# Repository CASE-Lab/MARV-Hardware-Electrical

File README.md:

# MARV-Hardware-Electrical
Contains the electrical design files fo the MARV system. These includes the PCBs and system wiring diagram and specific wire function diagram. Some of the PCB projects includes a component library, otherwise the CASE-Association case-eagle-libraries have been used, found here: https://github.com/CASE-Association/case-eagle-libraries.git

This project uses both Eagle and KiCad ECAD programs. This is shown by folder names.

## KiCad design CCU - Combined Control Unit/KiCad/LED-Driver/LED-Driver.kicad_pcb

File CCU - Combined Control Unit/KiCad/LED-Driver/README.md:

# MIDI Fuse LED Driver

Led driver with integrated eFuse and PWM dimming in a MIDI fuse format. Provides undervoltage cutoff for battery protection and a low standby current of 30 uA.

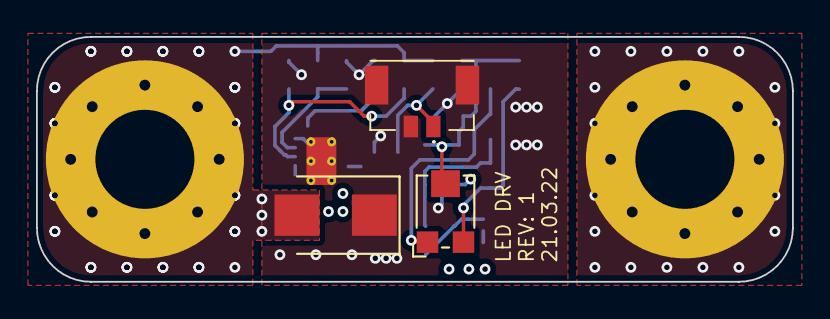
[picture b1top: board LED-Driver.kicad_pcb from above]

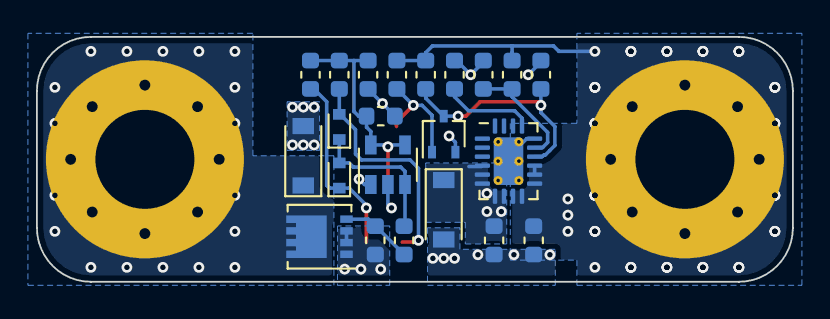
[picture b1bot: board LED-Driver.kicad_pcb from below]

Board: 4 copper layers, 42.0 x 13.6 mm, 27 parts (22 on the bottom side), 13 nets.

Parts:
C1, C2: 0.1 uF; C_0603_1608Metric
C3: 2.2uF 16V; C_0603_1608Metric
C4: ?; C_0603_1608Metric
D1, D5: D_Schottky; D_SOD-123
D2, D3: RB751S40T5G; D_SOD-523
D4: D_TVS; D_SMB
J1, J2: Conn_01x01; MountingHole_5.5mm_Pad_Via
J3: Conn_01x02; Molex_Micro-Lock_5055680271_1x02_P1.25_Vertical
Q1: 2N7002PW; SOT-323_SC-70
Q2: DMP3013SFV; Diodes_PowerDI3333-8
R1: 130k; R_0603_1608Metric
R2, R5: 1.5M; R_0603_1608Metric
R3, R6, R9: 100k; R_0603_1608Metric
R4: 18k; R_0603_1608Metric
R7, R8: R; R_0603_1608Metric
R10: 1k; R_0603_1608Metric
RV1: 100k; Potentiometer_Bourns_TC33X_Vertical
U1: MIC1555YM5-TR; SOT-23-5
U2: TPS25940x-Q1; QFN-20-1EP_3x4mm_P0.5mm_EP1.65x2.65mm_ThermalVias

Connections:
+12V: C1.1, D1.1, Q2.1, Q2.2, Q2.3, R9.2, U1.1, U2.4, U2.5, U2.6, U2.7, U2.8
+BATT: C2.1, D4.2, J1.1, R2.1, R5.1, R6.1, U2.9, U2.10, U2.11, U2.12, U2.13
/GATE: Q2.4, R9.1, R10.1
/LED_OUT: D5.1, J2.1, Q2.5
/PWM: D2.2, D3.1, R10.2, U1.3
/TRG_THR: C3.1, C4.1, R7.2, R8.2, RV1.2, U1.4, U1.5
/eFuse/~EN: J3.1, Q1.1, R6.2
GND: C1.2, C2.2, C3.2, C4.2, D1.2, D4.1, D5.2, J3.2, J3.MP, Q1.2, R1.2, R3.2, R4.2, U1.2, U2.16, U2.21
unnamed: D2.1, R7.1, RV1.3
unnamed: D3.2, R8.1, RV1.1
unnamed: Q1.3, R1.1, R5.2, U2.14
unnamed: R2.2, R3.1, U2.15
unnamed: R4.1, U2.17

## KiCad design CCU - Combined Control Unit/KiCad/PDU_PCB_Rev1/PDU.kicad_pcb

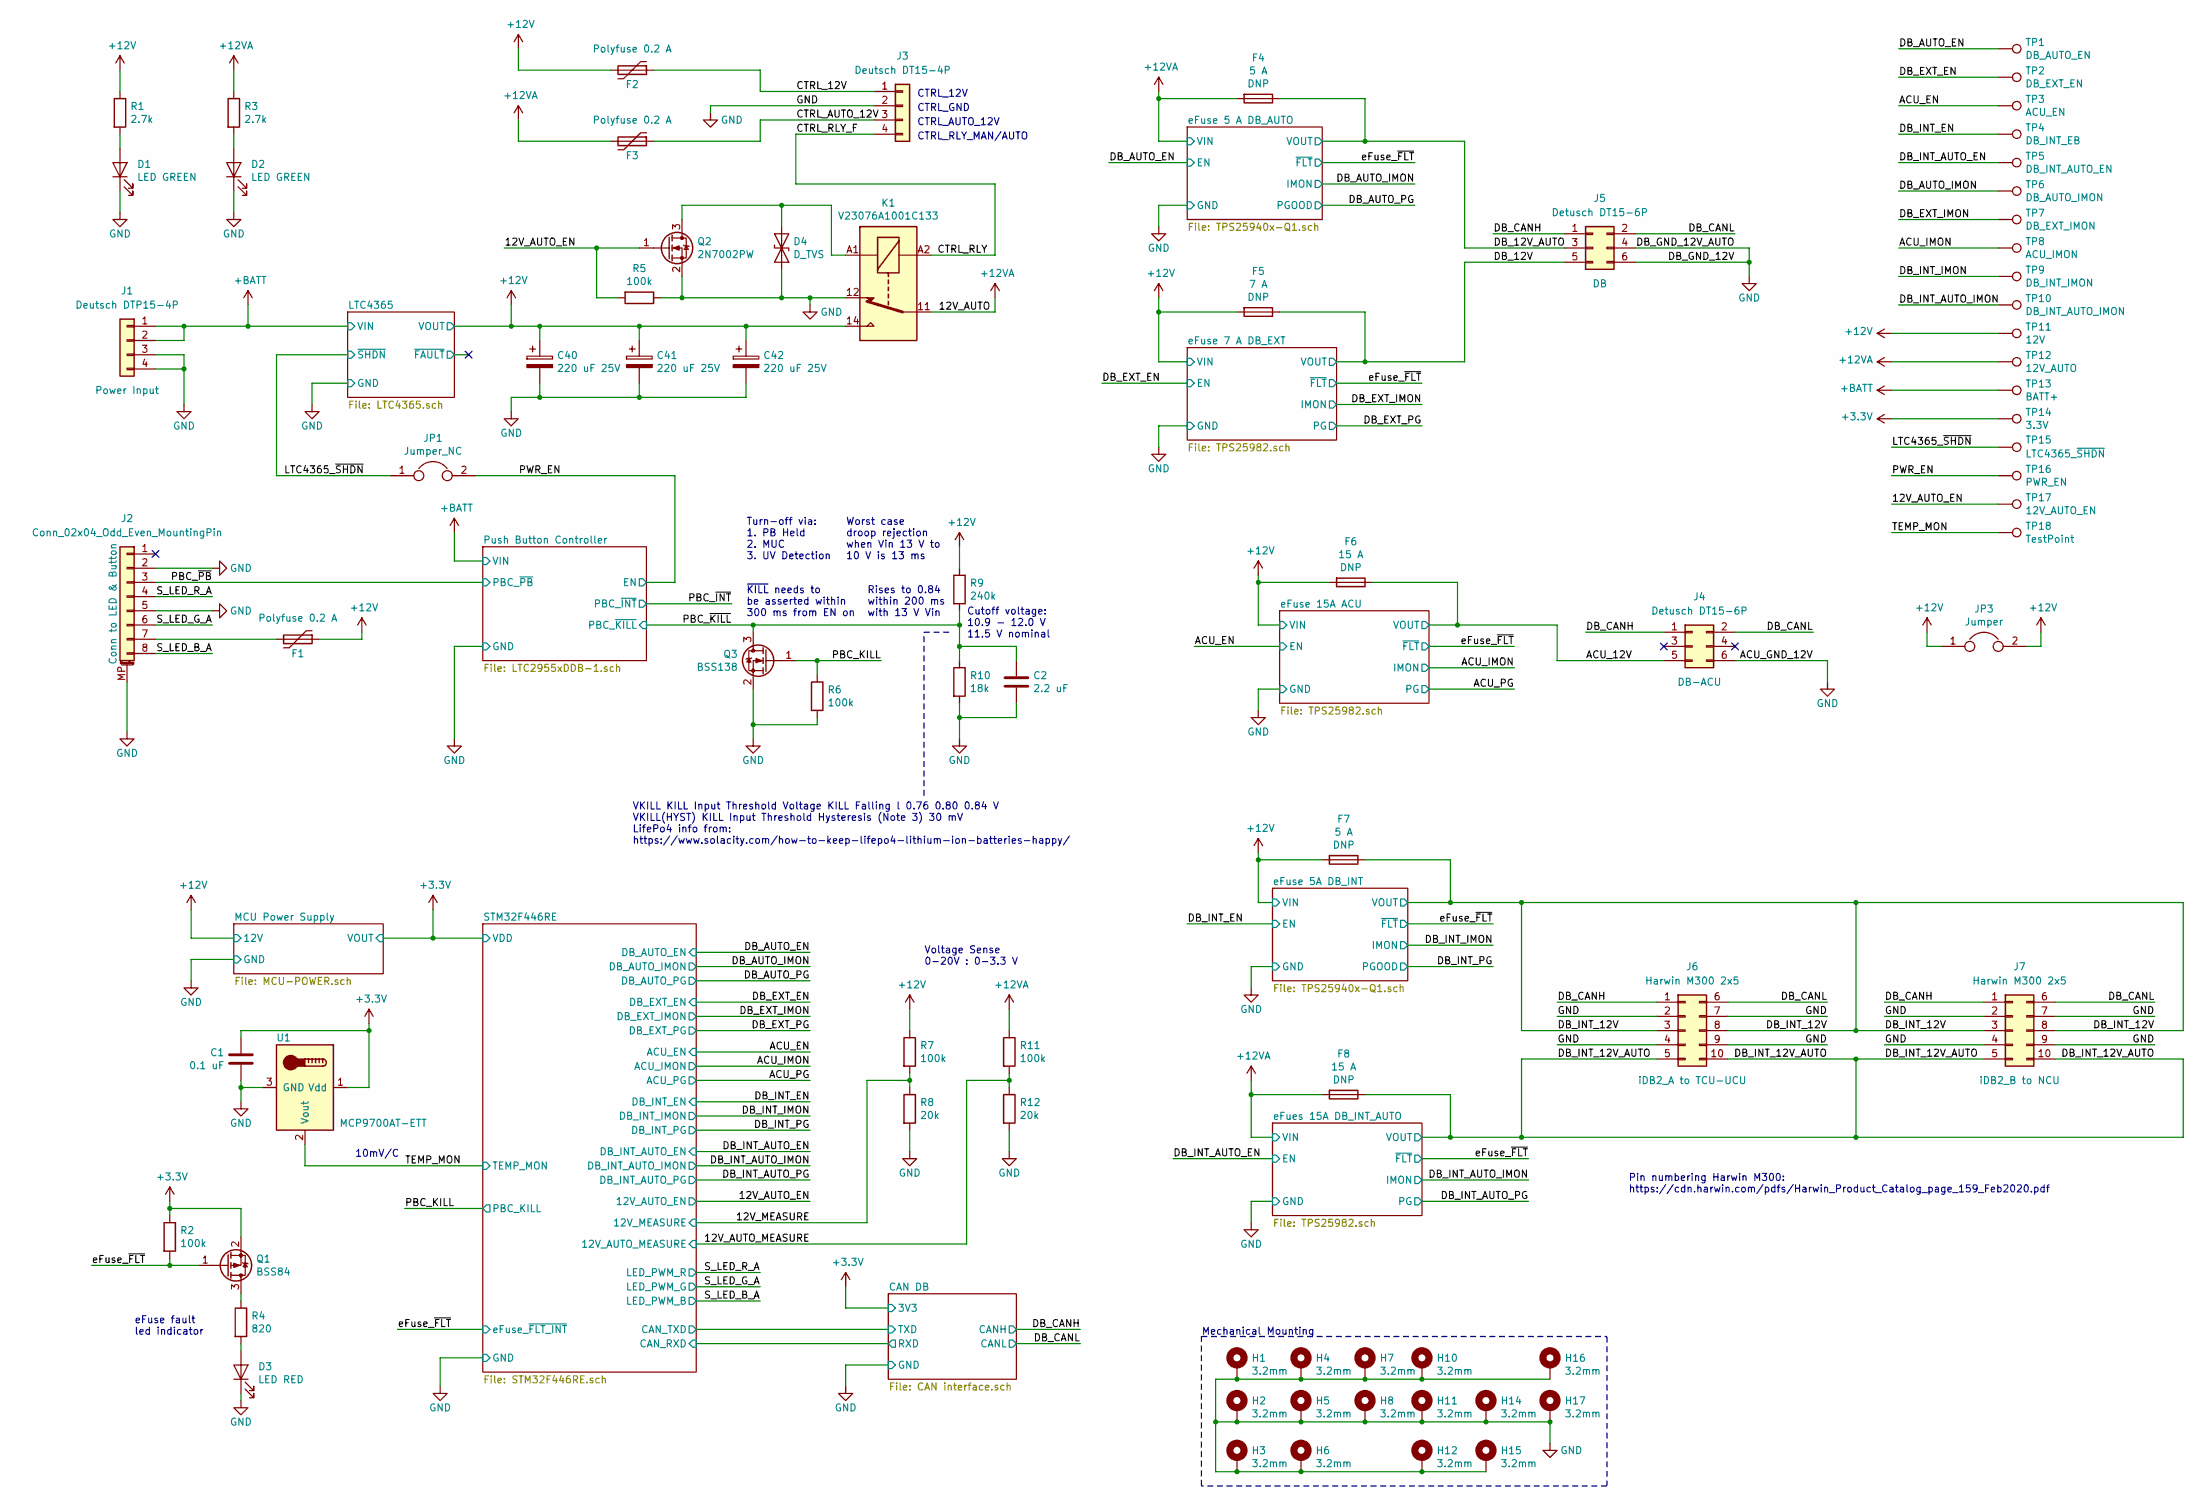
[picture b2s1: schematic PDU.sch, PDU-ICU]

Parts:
C1: 0.1 uF; C_0603_1608Metric
C2: 2.2 uF; C_0603_1608Metric
C40, C41, C42: 220 uF 25V; CP_Radial_D8.0mm_P3.50mm; MPN ESE227M025AG3AA
D1, D2: LED GREEN; LED_0603_1608Metric
D3: LED RED; LED_0603_1608Metric
D4: D_TVS; D_SMB; MPN TPSMB20CA
F1, F2, F3: Polyfuse 0.2 A; R_1206_3216Metric; MPN NANOSMDC020F-2
F4, F7: 5 A; Fuse_2010_5025Metric_Pad1.52x2.65mm_HandSolder; MPN 0453005
F5: 7 A; Fuse_2010_5025Metric_Pad1.52x2.65mm_HandSolder; MPN 0453007
F6, F8: 15 A; Fuse_2010_5025Metric_Pad1.52x2.65mm_HandSolder; MPN 0453012
H1, H2, H3, H4, H5, H6, H7, H8, H10, H11, H12, H14, H15, H16, H17: 3.2mm; MountingHole_3.2mm_M3_Pad_Via
J1: Deutsch DTP15-4P; Deutsch_DTP15-4P_2x2
J2: Conn_02x04_Odd_Even_MountingPin; Molex_Micro-Lock_5054330871_2x4_P1.25_Vertical; MPN 538-505433-0871
J3: Deutsch DT15-4P; Deutsch_DT15-4P_2x2
J4, J5: Detusch DT15-6P; Detusch_DT15-6P_2x3
J6, J7: Harwin M300 2x5; Harwin_M300_M300MV31045M1_2x5_P3.0_Vertical
JP1: Jumper_NC; R_0603_1608Metric
JP3: Jumper; Keystone_5104; MPN 5104
K1: V23076A1001C133; TE_Relay_V23076A1001C133
Q1: BSS84; SOT-23; MPN BSS84
Q2: 2N7002PW; SOT-323_SC-70
Q3: BSS138; SOT-23
R1, R3: 2.7k; R_0603_1608Metric
R2, R5, R6, R7, R11: 100k; R_0603_1608Metric
R4: 820; R_0603_1608Metric
R8, R12: 20k; R_0603_1608Metric
R9: 240k; R_0603_1608Metric
R10: 18k; R_0603_1608Metric
TP1: DB_AUTO_EN; TestPoint_THTPad_D1.0mm_Drill0.5mm
TP2: DB_EXT_EN; TestPoint_THTPad_D1.0mm_Drill0.5mm
TP3: ACU_EN; TestPoint_THTPad_D1.0mm_Drill0.5mm
TP4: DB_INT_EB; TestPoint_THTPad_D1.0mm_Drill0.5mm
TP5: DB_INT_AUTO_EN; TestPoint_THTPad_D1.0mm_Drill0.5mm
TP6: DB_AUTO_IMON; TestPoint_THTPad_D1.0mm_Drill0.5mm
TP7: DB_EXT_IMON; TestPoint_THTPad_D1.0mm_Drill0.5mm
TP8: ACU_IMON; TestPoint_THTPad_D1.0mm_Drill0.5mm
TP9: DB_INT_IMON; TestPoint_THTPad_D1.0mm_Drill0.5mm
TP10: DB_INT_AUTO_IMON; TestPoint_THTPad_D1.0mm_Drill0.5mm
TP11: 12V; TestPoint_THTPad_D1.0mm_Drill0.5mm
TP12: 12V_AUTO; TestPoint_THTPad_D1.0mm_Drill0.5mm
TP13: BATT+; TestPoint_THTPad_D1.0mm_Drill0.5mm
TP14: 3.3V; TestPoint_THTPad_D1.0mm_Drill0.5mm
TP15: LTC4365_~SHDN; TestPoint_THTPad_D1.0mm_Drill0.5mm
TP16: PWR_EN; TestPoint_THTPad_D1.0mm_Drill0.5mm
TP17: 12V_AUTO_EN; TestPoint_THTPad_D1.0mm_Drill0.5mm
TP18: TestPoint; TestPoint_THTPad_D1.0mm_Drill0.5mm
U1: MCP9700AT-ETT; SOT-23; MPN MCP9700AT-E/TT

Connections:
+3V3: C1.1, Q1.2 (S), R2.1, TP14.1, U1.1 (Vdd); also elsewhere on the board
+12V: C40.1, C41.1, C42.1, F1.1, F2.2, F5.2, F6.2, F7.2, JP3.1, JP3.2, K1.14, R1.1, R7.1, R9.1, TP11.1; also elsewhere on the board
+12VA: F3.2, F4.2, F8.2, K1.11, R3.1, R11.1, TP12.1; also elsewhere on the board
+BATT: J1.1, J1.2, TP13.1; also elsewhere on the board
/12V_AUTO_EN: Q2.1 (G), R5.2, TP17.1; also elsewhere on the board
/12V_AUTO_MEASURE: R11.2, R12.1; also elsewhere on the board
/12V_MEASURE: R7.2, R8.1; also elsewhere on the board
/ACU_12V: F6.1, J4.5; also elsewhere on the board
/ACU_EN: TP3.1; also elsewhere on the board
/ACU_IMON: TP8.1; also elsewhere on the board
/CTRL_12V: F2.1, J3.1
/CTRL_AUTO_12V: F3.1, J3.3
/CTRL_RLY: J3.4, K1.A2
/DB_AUTO_EN: TP1.1; also elsewhere on the board
/DB_AUTO_IMON: TP6.1; also elsewhere on the board
/DB_CANH: J4.1, J5.1, J6.1, J7.1; also elsewhere on the board
/DB_CANL: J4.2, J5.2, J6.6, J7.6; also elsewhere on the board
/DB_EXT_EN: TP2.1; also elsewhere on the board
/DB_EXT_IMON: TP7.1; also elsewhere on the board
/DB_INT_AUTO_EN: TP5.1; also elsewhere on the board
/DB_INT_AUTO_IMON: TP10.1; also elsewhere on the board
/DB_INT_EN: TP4.1; also elsewhere on the board
/DB_INT_IMON: TP9.1; also elsewhere on the board
/LTC4365_~SHDN: JP1.1, TP15.1; also elsewhere on the board
/PBC_KILL: Q3.1 (G), R6.1; also elsewhere on the board
/PBC_~KILL: C2.1, Q3.3 (D), R9.2, R10.1; also elsewhere on the board
/PBC_~PB: J2.3; also elsewhere on the board
/PWR_EN: JP1.2, TP16.1; also elsewhere on the board
/S_LED_B_A: J2.8; also elsewhere on the board
/S_LED_G_A: J2.6; also elsewhere on the board
/S_LED_R_A: J2.4; also elsewhere on the board
/TEMP_MON: TP18.1, U1.2 (Vout); also elsewhere on the board
/eFuse_~FLT: Q1.1 (G), R2.2; also elsewhere on the board
GND: C1.2, C2.2, C40.2, C41.2, C42.2, D1.1 (K), D2.1 (K), D3.1 (K), D4.2 (A2), H1.1, H2.1, H3.1, H4.1, H5.1, H6.1, H7.1, H8.1, H10.1, H11.1, H12.1, H14.1, H15.1, H16.1, H17.1, J1.3, J1.4, J2.2, J2.5, J2.MP (MountPin), J3.2, J4.6, J5.4, J5.6, J6.2, J6.4, J6.7, J6.9, J7.2, J7.4, J7.7, J7.9, K1.12, Q2.2 (S), Q3.2 (S), R5.1, R6.2, R8.2, R10.2, R12.2, U1.3 (GND); also elsewhere on the board
unnamed: D1.2 (A), R1.2
unnamed: D2.2 (A), R3.2
unnamed: D3.2 (A), R4.2
unnamed: D4.1 (A1), K1.A1, Q2.3 (D)
unnamed: F1.2, J2.7
unnamed: Q1.3 (D), R4.1

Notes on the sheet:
Mechanical Mounting
CTRL_12V
CTRL_GND
CTRL_AUTO_12V
CTRL_RLY_MAN/AUTO
Turn-off via: 1. PB Held 2. MUC 3. UV Detection
Pin numbering Harwin M300: https://cdn.harwin.com/pdfs/Harwin_Product_Catalog_page_159_Feb2020.pdf
eFuse fault led indicator
Voltage Sense 0-20V : 0-3.3 V
10mV/C
VKILL KILL Input Threshold Voltage KILL Falling l 0.76 0.80 0.84 V VKILL(HYST) KILL Input Threshold Hysteresis (Note 3) 30 mV LifePo4 info from: https://www.solacity.com/how-to-keep-lifepo4-lithium-ion-batteries-happy/
Cutoff voltage: 10.9 - 12.0 V 11.5 V nominal
~KILL~ needs to be asserted within 300 ms from EN on
Rises to 0.84 within 200 ms with 13 V Vin
Worst case droop rejection when Vin 13 V to 10 V is 13 ms

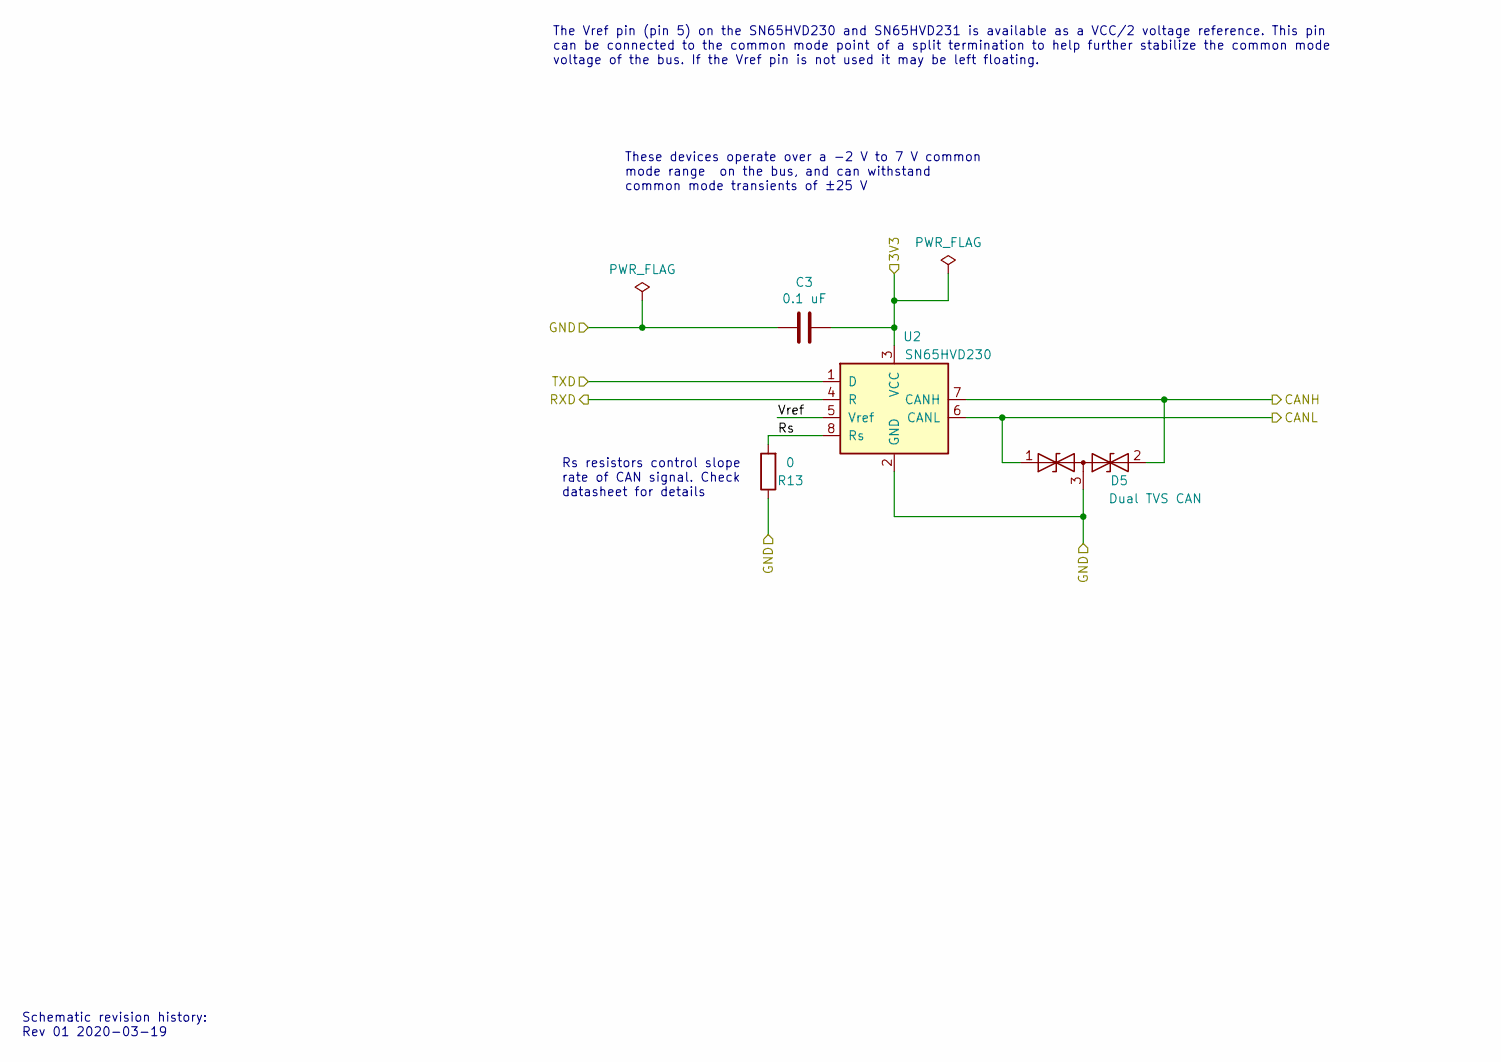
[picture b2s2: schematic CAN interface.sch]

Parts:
C3: 0.1 uF; C_0603_1608Metric
D5: Dual TVS CAN; SOT-23; MPN NUP2105L
R13: 0; R_0603_1608Metric
U2: SN65HVD230; SOIC-8_3.9x4.9mm_P1.27mm

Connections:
+3V3: C3.1, U2.3 (VCC); also elsewhere on the board
/CAN DB/Rs: R13.2, U2.8 (Rs)
/CAN DB/Vref: U2.5 (Vref)
/DB_CANH: D5.2 (A2), U2.7 (CANH); also elsewhere on the board
/DB_CANL: D5.1 (A1), U2.6 (CANL); also elsewhere on the board
/STM32F446RE/CAN_RXD: U2.4 (R); also elsewhere on the board
/STM32F446RE/CAN_TXD: U2.1 (D); also elsewhere on the board
GND: C3.2, D5.3 (common), R13.1, U2.2 (GND); also elsewhere on the board

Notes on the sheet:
These devices operate over a -2 V to 7 V common mode range on the bus, and can withstand common mode transients of ±25 V
Rs resistors control slope rate of CAN signal. Check datasheet for details
Schematic revision history: Rev 01 2020-03-19
The Vref pin (pin 5) on the SN65HVD230 and SN65HVD231 is available as a VCC/2 voltage reference. This pin can be connected to the common mode point of a split termination to help further stabilize the common mode voltage of the bus. If the Vref pin is not used it may be left floating.

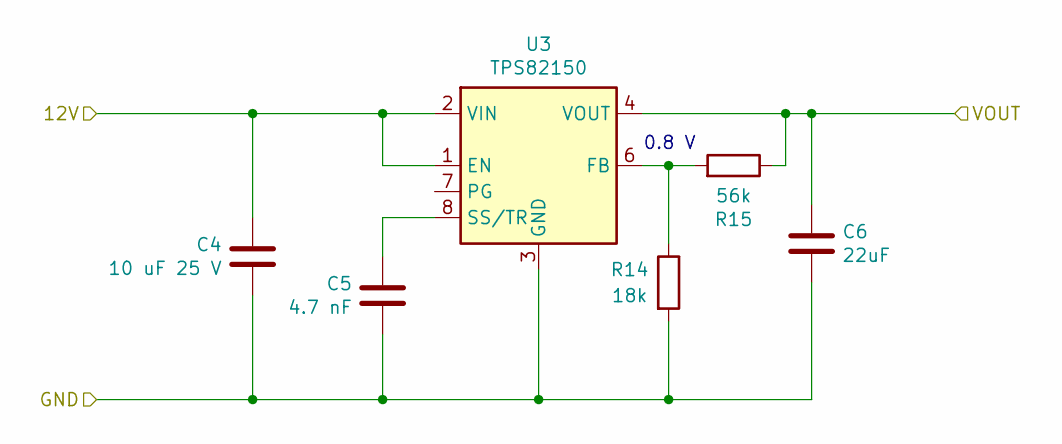
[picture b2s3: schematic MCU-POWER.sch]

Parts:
C4: 10 uF 25 V; C_1206_3216Metric
C5: 4.7 nF; C_0603_1608Metric
C6: 22uF; C_1206_3216Metric
R14: 18k; R_0603_1608Metric
R15: 56k; R_0603_1608Metric
U3: TPS82150; Texas_SIL0008D_MicroSiP-8-1EP_2.8x3mm_P0.65mm_EP1.1x1.9mm_T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; MPN TPS82150SILR

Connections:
+3V3: C6.1, R15.1, U3.4 (VOUT), U3.5 (VOUT); also elsewhere on the board
+12V: C4.1, U3.1 (EN), U3.2 (VIN); also elsewhere on the board
GND: C4.2, C5.2, C6.2, R14.2, U3.3 (GND), U3.9 (GND); also elsewhere on the board
unnamed: C5.1, U3.8 (SS/TR)
unnamed: R14.1, R15.2, U3.6 (FB)

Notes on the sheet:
0.8 V

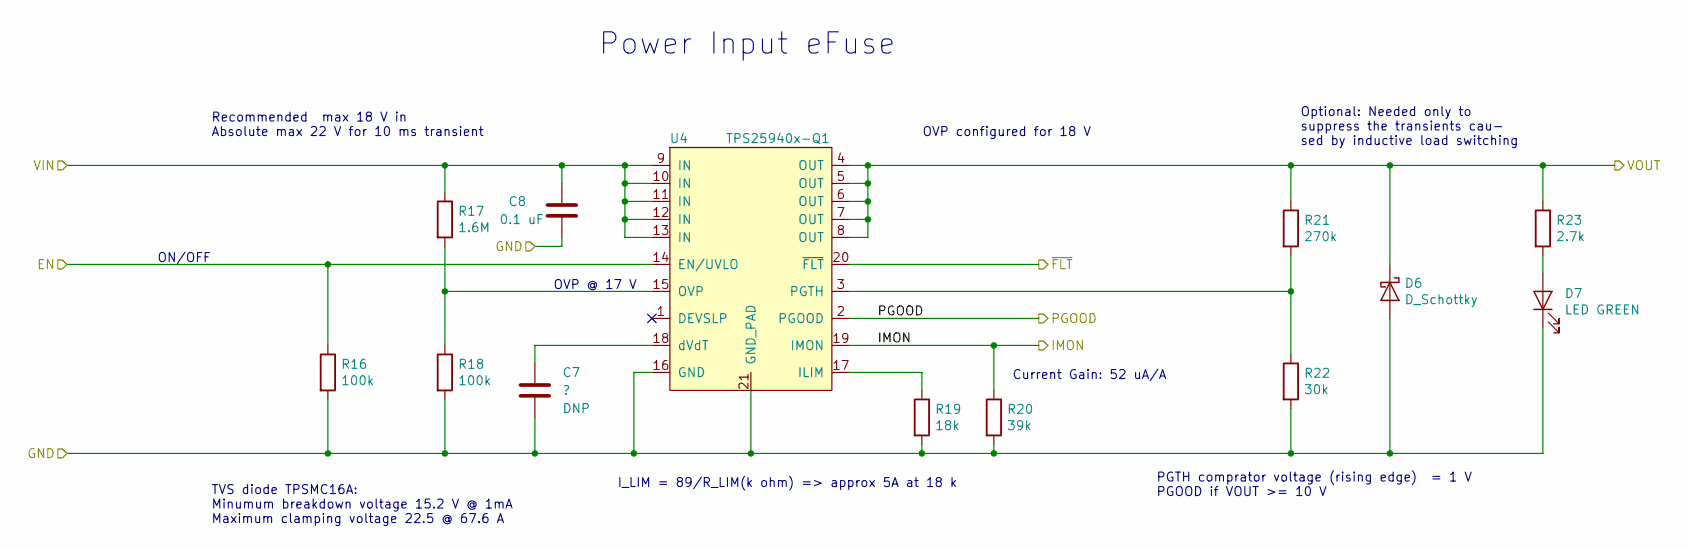
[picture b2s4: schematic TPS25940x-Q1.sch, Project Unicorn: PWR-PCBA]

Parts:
C7: ?; C_0603_1608Metric
C8: 0.1 uF; C_0603_1608Metric
D6: D_Schottky; D_SOD-123; MPN 1N5819HW
D17: LED GREEN; LED_0603_1608Metric
R16, R18: 100k; R_0603_1608Metric
R17: 1.6M; R_0603_1608Metric
R19: 18k; R_0603_1608Metric
R20: 39k; R_0603_1608Metric
R21: 270k; R_0603_1608Metric
R22: 30k; R_0603_1608Metric
R54: 2.7k; R_0603_1608Metric
U4: TPS25940x-Q1; QFN-20-1EP_3x4mm_P0.5mm_EP1.65x2.65mm_ThermalVias; MPN TPS25940LQRVCRQ1

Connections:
+12V: C8.1, R17.1, U4.9 (IN), U4.10 (IN), U4.11 (IN), U4.12 (IN), U4.13 (IN); also elsewhere on the board
/DB_INT_EN: R16.1, U4.14 (EN/UVLO); also elsewhere on the board
/DB_INT_IMON: R20.1, U4.19 (IMON); also elsewhere on the board
/DB_INT_PG: U4.2 (PGOOD); also elsewhere on the board
/eFuse_~FLT: U4.20 (~FLT); also elsewhere on the board
GND: C7.2, C8.2, D6.2 (A), D17.1 (K), R16.2, R18.2, R19.2, R20.2, R22.2, U4.16 (GND), U4.21 (GND_PAD); also elsewhere on the board
unnamed: C7.1, U4.18 (dVdT)
unnamed: D17.2 (A), R54.2
unnamed: R17.2, R18.1, U4.15 (OVP)
unnamed: R19.1, U4.17 (ILIM)
unnamed: R21.2, R22.1, U4.3 (PGTH)

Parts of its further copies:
C28: ?; C_0603_1608Metric
C29: 0.1 uF; C_0603_1608Metric
D7: LED GREEN; LED_0603_1608Metric
D16: D_Schottky; D_SOD-123; MPN 1N5819HW
R23: 2.7k; R_0603_1608Metric
R47, R49: 100k; R_0603_1608Metric
R48: 1.6M; R_0603_1608Metric
R50: 18k; R_0603_1608Metric
R51: 39k; R_0603_1608Metric
R52: 270k; R_0603_1608Metric
R53: 30k; R_0603_1608Metric
U10: TPS25940x-Q1; QFN-20-1EP_3x4mm_P0.5mm_EP1.65x2.65mm_ThermalVias; MPN TPS25940LQRVCRQ1

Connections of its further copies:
+12VA: C29.1, R48.1, U10.9 (IN), U10.10 (IN), U10.11 (IN), U10.12 (IN), U10.13 (IN); also elsewhere on the board
/DB_AUTO_EN: R47.1, U10.14 (EN/UVLO); also elsewhere on the board
/DB_AUTO_IMON: R51.1, U10.19 (IMON); also elsewhere on the board
/DB_AUTO_PG: U10.2 (PGOOD); also elsewhere on the board
/eFuse_~FLT: U10.20 (~FLT); also elsewhere on the board
GND: C28.2, C29.2, D7.1 (K), D16.2 (A), R47.2, R49.2, R50.2, R51.2, R53.2, U10.16 (GND), U10.21 (GND_PAD); also elsewhere on the board
unnamed: C28.1, U10.18 (dVdT)
unnamed: D7.2 (A), R23.2
unnamed: R48.2, R49.1, U10.15 (OVP)
unnamed: R50.1, U10.17 (ILIM)
unnamed: R52.2, R53.1, U10.3 (PGTH)

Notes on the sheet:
ON/OFF
Power Input eFuse
Recommended max 18 V in Absolute max 22 V for 10 ms transient
I_LIM = 89/R_LIM(k ohm) => approx 5A at 18 k
PGTH comprator voltage (rising edge) = 1 V PGOOD if VOUT >= 10 V
OVP configured for 18 V
Optional: Needed only to suppress the transients cau- sed by inductive load switching
TVS diode TPSMC16A: Minumum breakdown voltage 15.2 V @ 1mA Maximum clamping voltage 22.5 @ 67.6 A
OVP @ 17 V
Current Gain: 52 uA/A

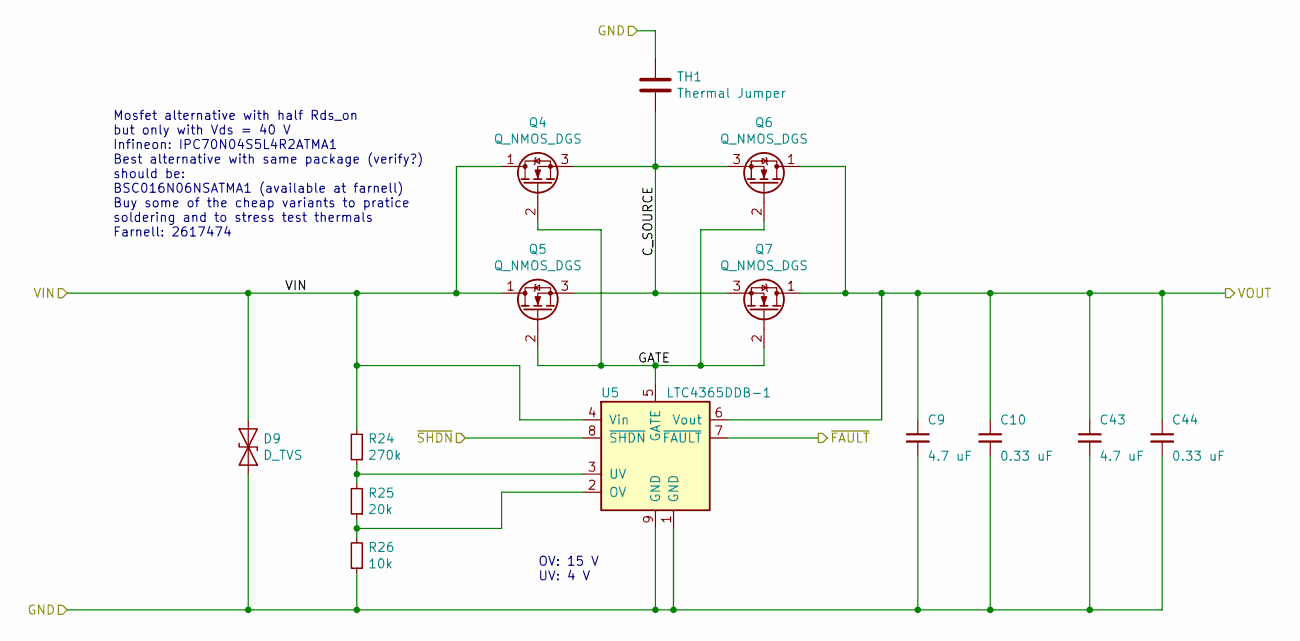
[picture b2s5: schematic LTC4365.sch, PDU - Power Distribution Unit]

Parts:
C9, C43: 4.7 uF; C_1206_3216Metric; MPN 12063C475K4T2A
C10, C44: 0.33 uF; C_0805_2012Metric
D9: D_TVS; D_SMC; MPN 5.0SMDJ24CA-Q
Q4, Q5, Q6, Q7: Q_NMOS_DGS; TDSON-8-1; MPN BSC016N06NSATMA1
R24: 270k; R_0603_1608Metric
R25: 20k; R_0603_1608Metric
R26: 10k; R_0603_1608Metric
TH1: Thermal Jumper; R_0612_1632Metric; MPN THJP0612AST1
U5: LTC4365DDB-1; DFN-8-1EP_2x3mm_P0.5mm_EP0.61x2.2mm; MPN LTC4365IDDB-1#TRMPBF

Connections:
+12V: C9.1, C10.1, C43.1, C44.1, Q6.1 (D), Q7.1 (D), U5.6 (Vout); also elsewhere on the board
+BATT: D9.1 (A1), Q4.1 (D), Q5.1 (D), R24.2, U5.4 (Vin); also elsewhere on the board
/LTC4365/C_SOURCE: Q4.3 (S), Q5.3 (S), Q6.3 (S), Q7.3 (S), TH1.2
/LTC4365/GATE: Q4.2 (G), Q5.2 (G), Q6.2 (G), Q7.2 (G), U5.5 (GATE)
/LTC4365/~FAULT: U5.7 (~FAULT)
/LTC4365_~SHDN: U5.8 (~SHDN); also elsewhere on the board
GND: C9.2, C10.2, C43.2, C44.2, D9.2 (A2), R26.1, TH1.1, U5.1 (GND), U5.9 (GND); also elsewhere on the board
unnamed: R24.1, R25.2, U5.3 (UV)
unnamed: R25.1, R26.2, U5.2 (OV)

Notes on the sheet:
OV: 15 V UV: 4 V
Mosfet alternative with half Rds_on but only with Vds = 40 V Infineon: IPC70N04S5L4R2ATMA1 Best alternative with same package (verify?) should be: BSC016N06NSATMA1 (available at farnell) Buy some of the cheap variants to pratice soldering and to stress test thermals Farnell: 2617474

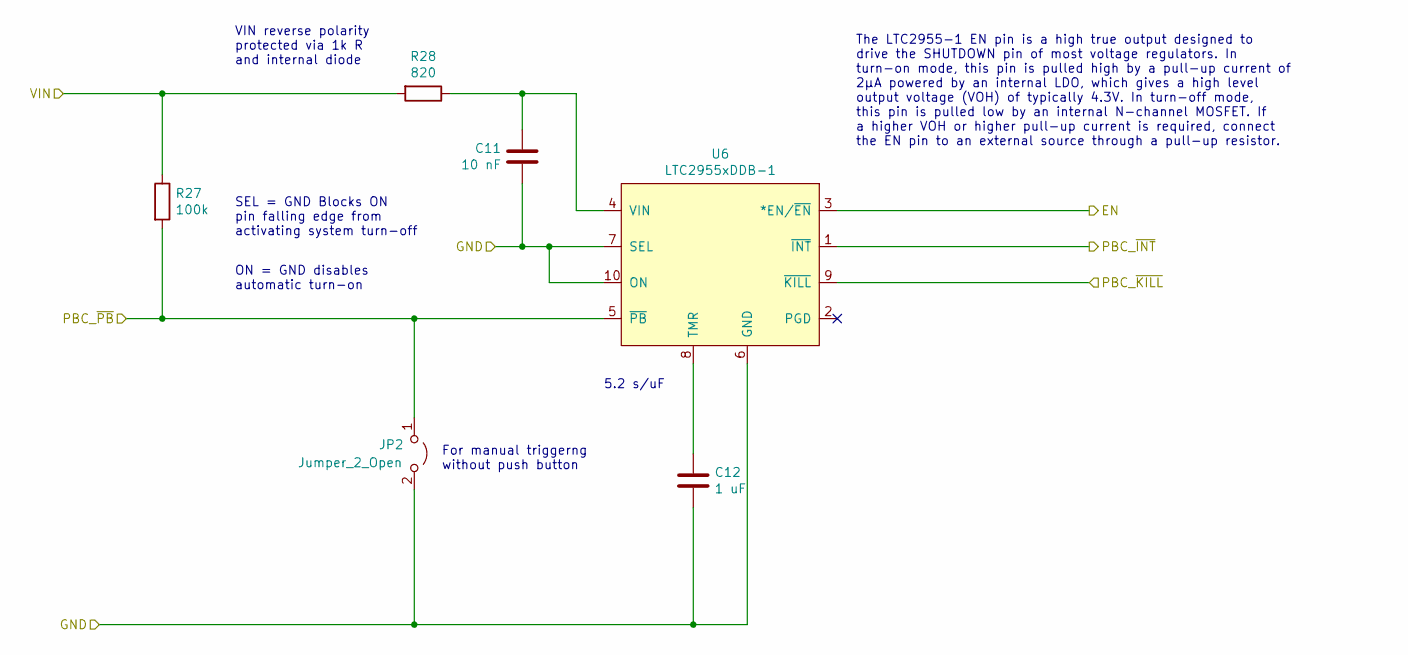
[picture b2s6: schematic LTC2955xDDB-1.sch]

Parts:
C11: 10 nF; C_0603_1608Metric
C12: 1 uF; C_0603_1608Metric
JP2: Jumper_2_Open; TestPoint_2Pads_Pitch2.54mm_Drill0.8mm
R27: 100k; R_0603_1608Metric
R28: 820; R_0603_1608Metric
U6: LTC2955xDDB-1; DFN-10-1EP_2x3mm_P0.5mm_EP0.64x2.4mm

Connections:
+BATT: R27.1, R28.2; also elsewhere on the board
/PBC_~INT: U6.1 (~INT)
/PBC_~KILL: U6.9 (~KILL); also elsewhere on the board
/PBC_~PB: JP2.1 (A), R27.2, U6.5 (~PB); also elsewhere on the board
/PWR_EN: U6.3 (*EN/~EN); also elsewhere on the board
GND: C11.2, C12.2, JP2.2 (B), U6.6 (GND), U6.7 (SEL), U6.10 (ON); also elsewhere on the board
unnamed: C11.1, R28.1, U6.4 (VIN)
unnamed: C12.1, U6.8 (TMR)

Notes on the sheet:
SEL = GND Blocks ON pin falling edge from activating system turn-off
5.2 s/uF
The LTC2955-1 EN pin is a high true output designed to drive the SHUTDOWN pin of most voltage regulators. In turn-on mode, this pin is pulled high by a pull-up current of 2µA powered by an internal LDO, which gives a high level output voltage (VOH) of typically 4.3V. In turn-off mode, this pin is p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
VIN reverse polarity protected via 1k R and internal diode
ON = GND disables automatic turn-on
For manual triggerng without push button

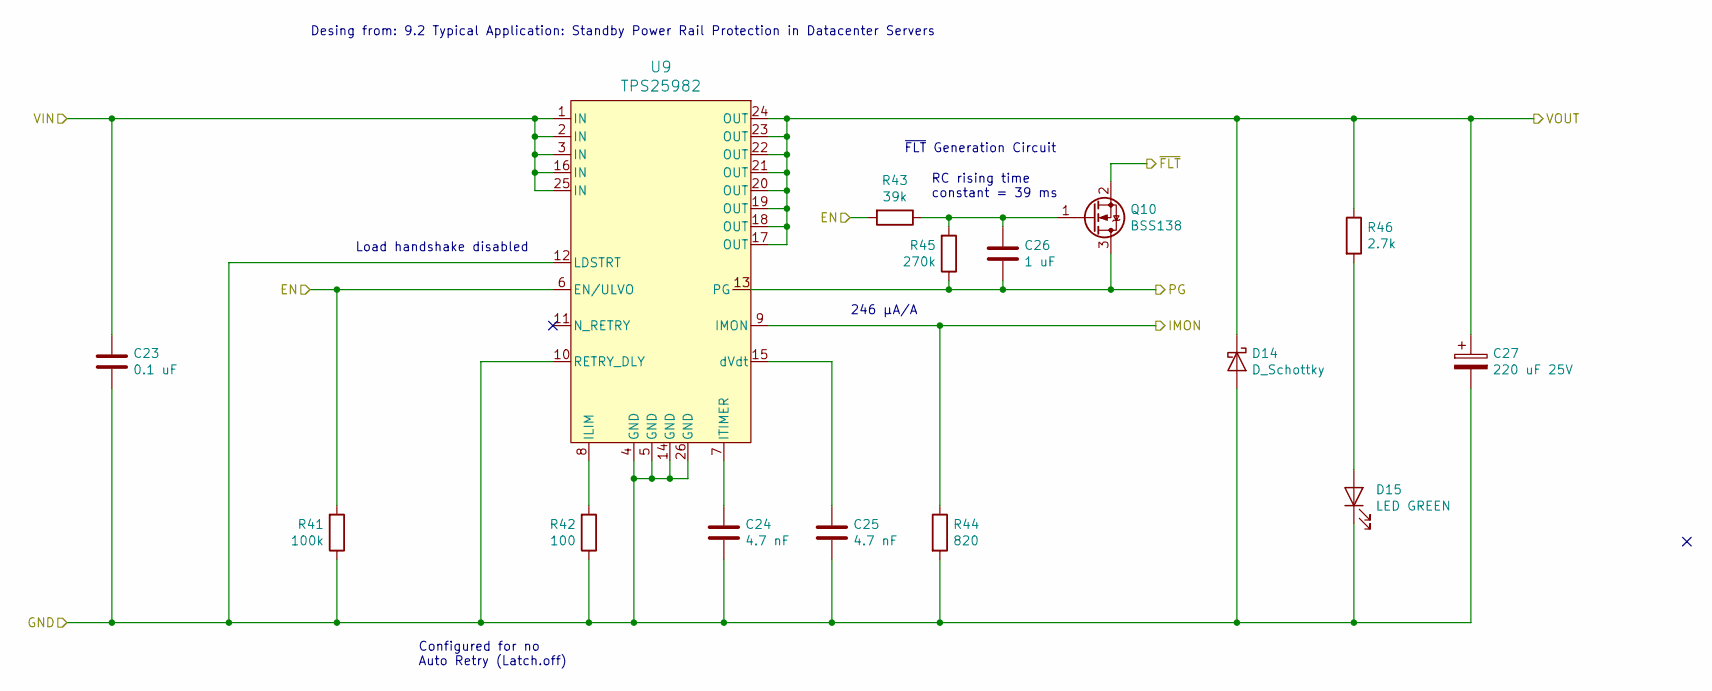
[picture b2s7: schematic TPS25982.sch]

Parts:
C13: 0.1 uF; C_0603_1608Metric
C14, C15: 4.7 nF; C_0603_1608Metric
C16: 1 uF; C_0603_1608Metric
C17: 220 uF 25V; CP_Radial_D8.0mm_P3.50mm; MPN ESE227M025AG3AA
D10: D_Schottky; D_SOD-123; MPN 1N5819HW
D15: LED GREEN; LED_0603_1608Metric
Q8: BSS138; SOT-23
R29: 100k; R_0603_1608Metric
R30: 100; R_0603_1608Metric
R31: 39k; R_0603_1608Metric
R32: 820; R_0603_1608Metric
R33: 270k; R_0603_1608Metric
R46: 2.7k; R_0603_1608Metric
U7: TPS25982; TPS259824ONRGET; MPN TPS259824ONRGET

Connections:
+12VA: C13.2, U7.1 (IN), U7.2 (IN), U7.3 (IN), U7.16 (IN), U7.25 (IN); also elsewhere on the board
/DB_INT_AUTO_EN: R29.2, R31.2, U7.6 (EN/ULVO); also elsewhere on the board
/DB_INT_AUTO_IMON: R32.1, U7.9 (IMON); also elsewhere on the board
/DB_INT_AUTO_PG: C16.1, Q8.3 (D), R33.1, U7.13 (PG); also elsewhere on the board
/eFuse_~FLT: Q8.2 (S); also elsewhere on the board
GND: C13.1, C14.2, C15.2, C17.2, D10.2 (A), D15.1 (K), R29.1, R30.1, R32.2, U7.4 (GND), U7.5 (GND), U7.10 (RETRY_DLY), U7.12 (LDSTRT), U7.14 (GND), U7.26 (GND); also elsewhere on the board
unnamed: C14.1, U7.7 (ITIMER)
unnamed: C15.1, U7.15 (dVdt)
unnamed: C16.2, Q8.1 (G), R31.1, R33.2
unnamed: D15.2 (A), R46.2
unnamed: R30.2, U7.8 (ILIM)

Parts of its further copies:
C18, C23: 0.1 uF; C_0603_1608Metric
C19, C20, C24, C25: 4.7 nF; C_0603_1608Metric
C21, C26: 1 uF; C_0603_1608Metric
C22, C27: 220 uF 25V; CP_Radial_D8.0mm_P3.50mm; MPN ESE227M025AG3AA
D11, D13: LED GREEN; LED_0603_1608Metric
D12, D14: D_Schottky; D_SOD-123; MPN 1N5819HW
Q9, Q10: BSS138; SOT-23
R34, R40: 2.7k; R_0603_1608Metric
R35, R41: 100k; R_0603_1608Metric
R36, R42: 100; R_0603_1608Metric
R37, R43: 39k; R_0603_1608Metric
R38, R44: 820; R_0603_1608Metric
R39, R45: 270k; R_0603_1608Metric
U8, U9: TPS25982; TPS259824ONRGET; MPN TPS259824ONRGET

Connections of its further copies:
+12V: C18.2, C23.2, U8.1 (IN), U8.2 (IN), U8.3 (IN), U8.16 (IN), U8.25 (IN), U9.1 (IN), U9.2 (IN), U9.3 (IN), U9.16 (IN), U9.25 (IN); also elsewhere on the board
/ACU_12V: C22.1, D12.1 (K), R40.1, U8.17 (OUT), U8.18 (OUT), U8.19 (OUT), U8.20 (OUT), U8.21 (OUT), U8.22 (OUT), U8.23 (OUT), U8.24 (OUT); also elsewhere on the board
/ACU_EN: R35.2, R37.2, U8.6 (EN/ULVO); also elsewhere on the board
/ACU_IMON: R38.1, U8.9 (IMON); also elsewhere on the board
/ACU_PG: C21.1, Q9.3 (D), R39.1, U8.13 (PG); also elsewhere on the board
/DB_EXT_EN: R41.2, R43.2, U9.6 (EN/ULVO); also elsewhere on the board
/DB_EXT_IMON: R44.1, U9.9 (IMON); also elsewhere on the board
/DB_EXT_PG: C26.1, Q10.3 (D), R45.1, U9.13 (PG); also elsewhere on the board
/eFuse_~FLT: Q9.2 (S), Q10.2 (S); also elsewhere on the board
GND: C18.1, C19.2, C20.2, C22.2, C23.1, C24.2, C25.2, C27.2, D11.1 (K), D12.2 (A), D13.1 (K), D14.2 (A), R35.1, R36.1, R38.2, R41.1, R42.1, R44.2, U8.4 (GND), U8.5 (GND), U8.10 (RETRY_DLY), U8.12 (LDSTRT), U8.14 (GND), U8.26 (GND), U9.4 (GND), U9.5 (GND), U9.10 (RETRY_DLY), U9.12 (LDSTRT), U9.14 (GND), U9.26 (GND); also elsewhere on the board
unnamed: C19.1, U8.7 (ITIMER)
unnamed: C20.1, U8.15 (dVdt)
unnamed: C21.2, Q9.1 (G), R37.1, R39.2
unnamed: C24.1, U9.7 (ITIMER)
unnamed: C25.1, U9.15 (dVdt)
unnamed: C26.2, Q10.1 (G), R43.1, R45.2
unnamed: D11.2 (A), R34.2
unnamed: D13.2 (A), R40.2
unnamed: R36.2, U8.8 (ILIM)
unnamed: R42.2, U9.8 (ILIM)

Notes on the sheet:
246 µA/A
Load handshake disabled
Configured for no Auto Retry (Latch.off)
Desing from: 9.2 Typical Application: Standby Power Rail Protection in Datacenter Servers
RC rising time constant = 39 ms
~FLT~ Generation Circuit

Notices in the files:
parts and their libraries:
Copyright 2016 Accelerated Designs. All rights reserved.
